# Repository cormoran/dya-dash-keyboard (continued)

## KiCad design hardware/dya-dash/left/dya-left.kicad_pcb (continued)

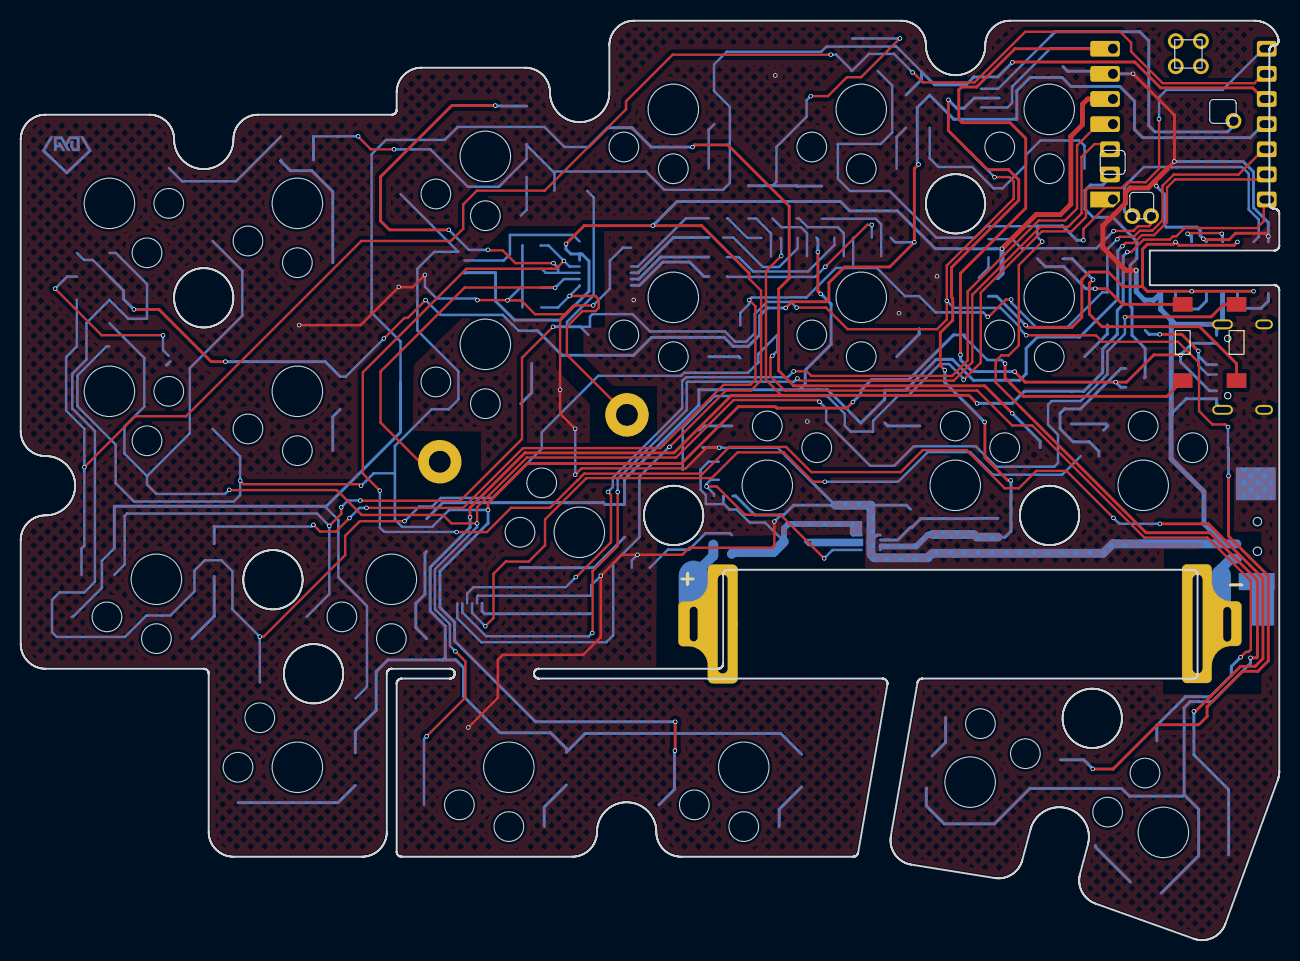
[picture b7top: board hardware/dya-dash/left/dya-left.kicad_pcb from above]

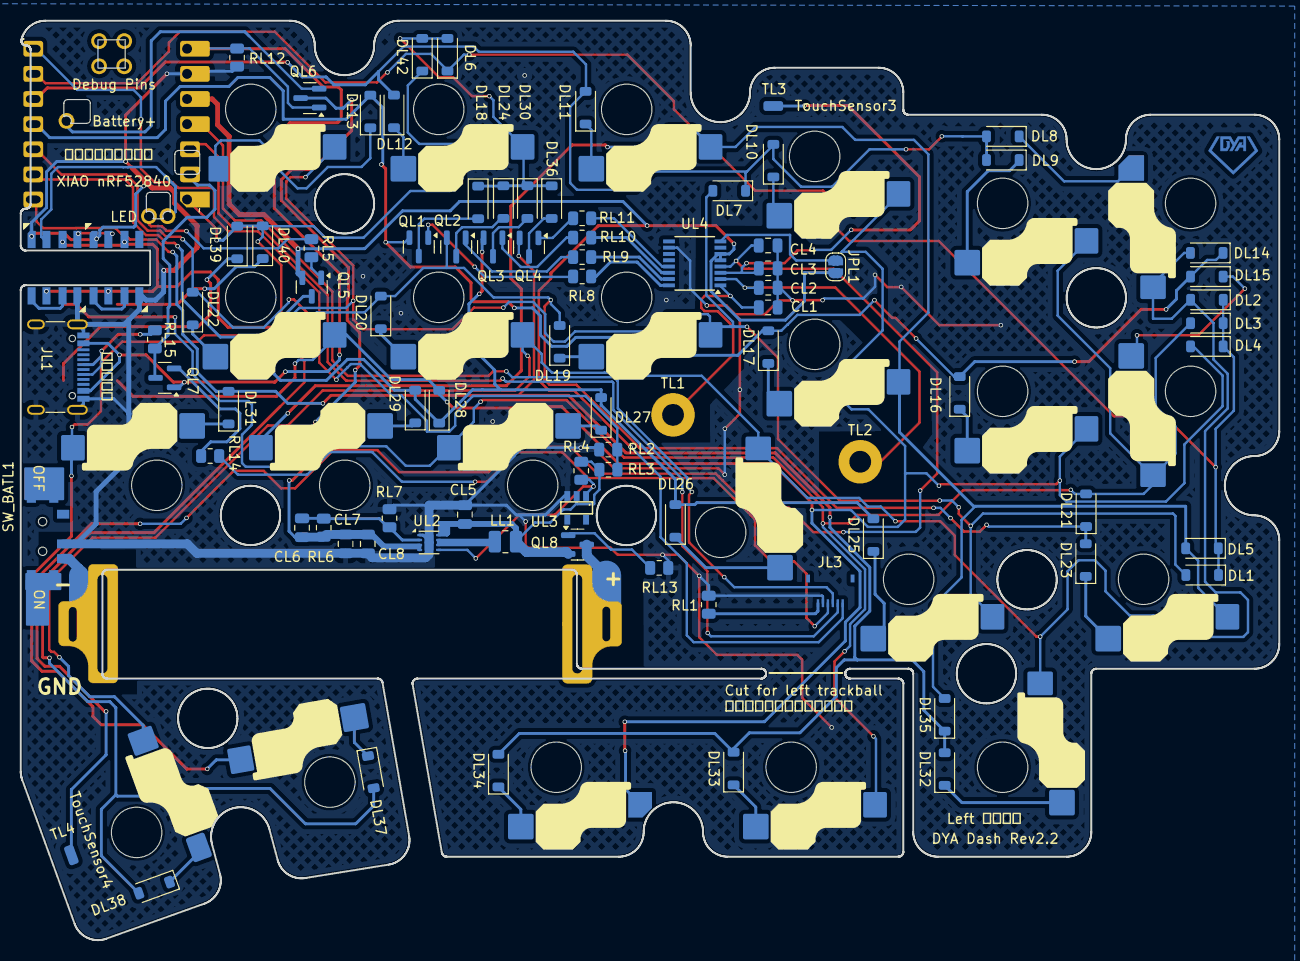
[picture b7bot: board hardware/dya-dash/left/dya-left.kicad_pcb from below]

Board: 2 copper layers, 127.2 x 92.9 mm, 115 parts (110 on the bottom side), 82 nets.

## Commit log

2025-05-10 Add dependent submodules
2025-05-10 Add PCB design
2025-05-10 update dependency
2025-05-10 Add dya dash firmware
2025-05-10 Add readme and LICENSE
2025-05-10 Add readme and pictures
2025-05-10 Support ZMK Studio
2025-05-13 Add initial build guide
2025-05-13 Add case data
2025-05-13 Add initial feature guide
2025-05-14 Improve build guide and feature guide
2025-05-14 Fix default layer bug and configure shorter setting save debounce
2025-05-15 Add warning for damaging top case in build guide
2025-05-16 Remove icon from top plate
2025-05-16 Link to latest firmware, fix description for ZMK Studio usage
2025-05-17 Add west.yml for user config
2025-05-17 test
2025-05-17 use https for submodule
2025-05-17 Remove zmk-driver-animation & zmk-driver-ext-power-transient to convert to submodule
2025-05-17 Add zmk-driver-animation & zmk-driver-ext-power-transient as submodule
2025-05-17 Remove zmk-keyboard-dya-dash to replace with submodule
2025-05-17 Add zmk-keyboard-dya-dash as submodule
2025-05-17 Remove firmware submodules once
2025-05-17 Re-add submodules by rearranging directory
2025-06-15 Finalize v2
2025-06-15 Update README and build guide (building) for v2
2025-06-15 Add case for V2.0
2025-06-16 Update guide for v2
2025-06-16 Update final figures and parts figures
2025-06-20 Add warning for FFC cable
2025-06-21 Add initial document site
2025-06-22 Add guide for left trackball
2025-06-22 Improve feature guide
2025-06-22 Add tracking to document site
2025-06-27 Improve FFC cable related documents and add warning2 for ffc
2025-07-24 Add note about battery pin
2025-07-26 Fix build guide order
2025-07-26 Add one more studio unlock command for dual trackball
2025-07-26 Update about trackball color
2025-07-27 Improve keymap customize guide about no arrow key model
2025-08-10 Update about trackball case improvement
2025-08-10 Update case design for V2
2025-08-11 Change FFC connector direction for arrow model
2025-08-11 Update case build guide for POM ball supported trackball case
2025-08-15 Improve build guide - Update kit contents section based on the latest packing style with figures - Fix many typo/unclear explanations - Add troubleshooting section
2025-08-15 Add guide for switch pad & warning for power switch cover
2025-11-14 Add the latest case model
2025-11-14 Add missing parts
2025-11-16 Add bottom case for left trackball
2025-11-18 Add document for using ZMK
2026-03-26 Add V3 model and build guide
2026-03-26 Fix booth link and header, update version info
2026-03-28 Fix docs for v3
2026-03-29 Update docs for 24mm ball
2026-04-05 Update documents for V3 and DYA Studio
